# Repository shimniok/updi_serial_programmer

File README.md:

# updi_serial_programmer
USB to Serial UPDI programmer for Atmel ATtiny microcontrollers

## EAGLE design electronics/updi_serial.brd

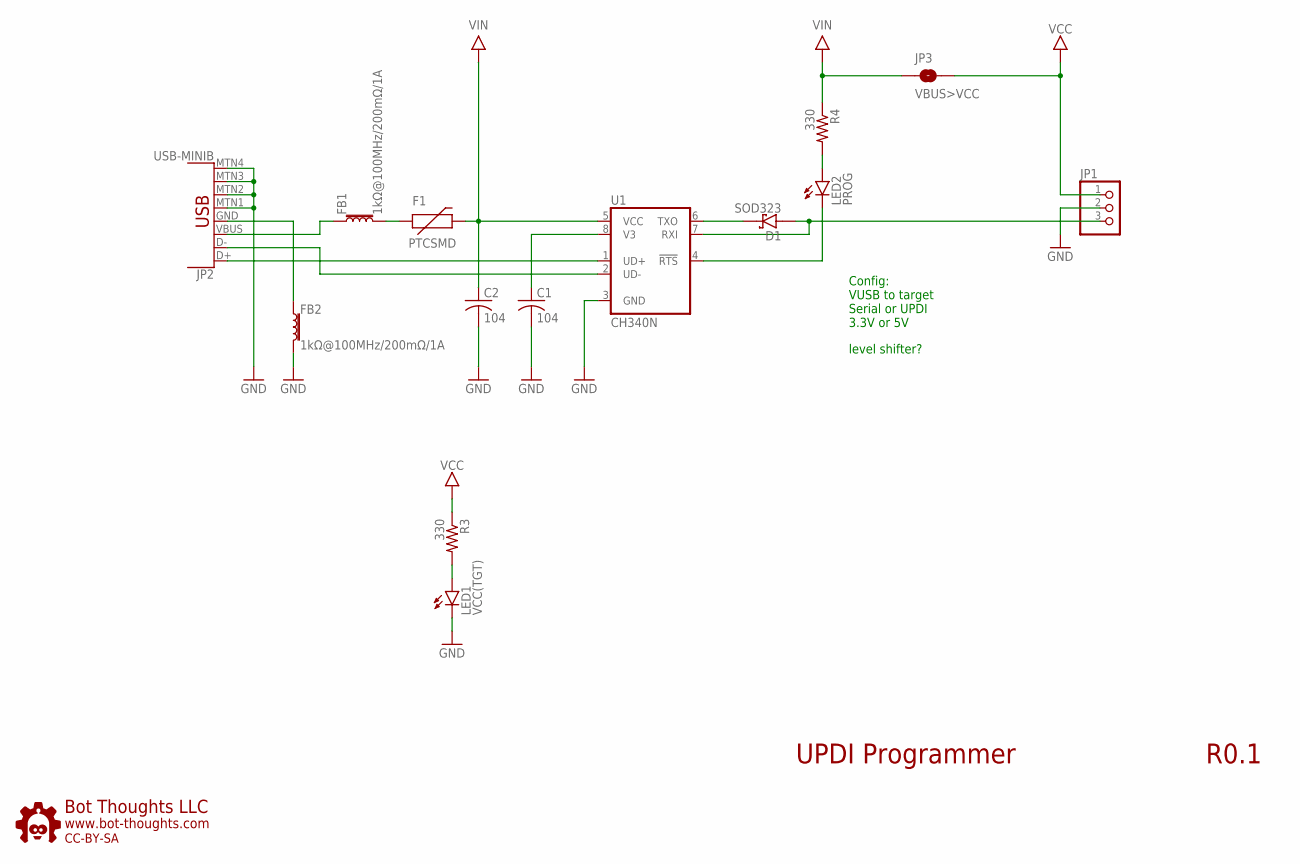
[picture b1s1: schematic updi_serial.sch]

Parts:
C1, C2: 104; 0603
D1: SOD323; SOD123FL
F1: PTCSMD; PTC-1206
FB1, FB2: 1kΩ@100MHz/200mΩ/1A; 0603
JP1: PINHD-1X03_2.54-S; 1X03-S
JP2: USB-MINIB
JP3: VBUS>VCC; JUMPER-PIN-0.1IN
LED1: VCC(TGT); CHIPLED_1206
LED2: PROG; CHIPLED_1206
R3, R4: 330; 0603
U1: CH340N; SOIC8N
U$5: BTLOGO-LOGO-SM; BTLOGOS

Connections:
DM: JP2.D-, U1.2 (UD-)
DP: JP2.D+, U1.1 (UD+)
GND: C1.2 (-), C2.2 (-), FB2.2, JP1.2, JP2.MTN1 (SHIELD1), JP2.MTN2 (SHIELD2), JP2.MTN3 (SHIELD3), JP2.MTN4 (SHIELD4), LED1.C, U1.3 (GND)
unnamed: FB1.1, JP2.VBUS
unnamed: F1.1, FB1.2
unnamed: D1.C, U1.6 (TXO)
unnamed: LED2.C, U1.4 (!RTS)
unnamed: LED2.A, R4.2
unnamed: LED1.A, R3.2
unnamed: FB2.1, JP2.GND
unnamed: C1.1 (+), U1.8 (V3)
UPDI: D1.A, JP1.3, U1.7 (RXI)
VCC: JP1.1, JP3.2, R3.1
VIN: C2.1 (+), F1.2, JP3.1, R4.1, U1.5 (VCC)

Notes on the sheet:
level shifter?
UPDI Programmer
R0.1
Config: VUSB to target Serial or UPDI 3.3V or 5V

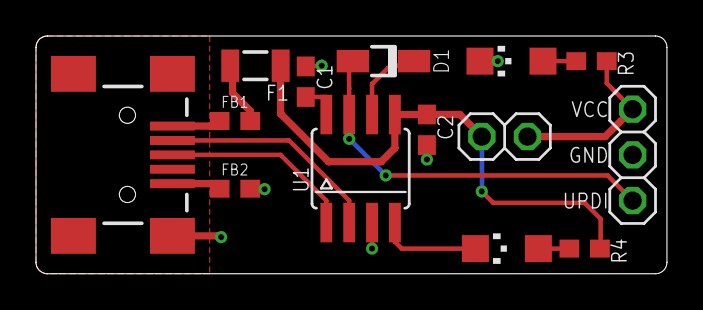
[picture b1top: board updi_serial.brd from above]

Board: 2 copper layers, 35.1 x 13.2 mm, 15 parts (1 on the bottom side), 14 nets.

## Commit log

2022-04-13 initial version
2022-04-13 update bottom silk
2022-04-13 changed pin hdr package, updated silk
2022-04-15 replaced solder jmpr with pin hdr, layout changes, pwr led indicates target pwr now

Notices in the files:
electronics/updi_serial.brd:
cc-by-sa
parts and their libraries:
SparkFun-Coils: Licensing: Creative Commons ShareAlike 4.0 International - https://creativecommons.org/licenses/by-sa/4.0
